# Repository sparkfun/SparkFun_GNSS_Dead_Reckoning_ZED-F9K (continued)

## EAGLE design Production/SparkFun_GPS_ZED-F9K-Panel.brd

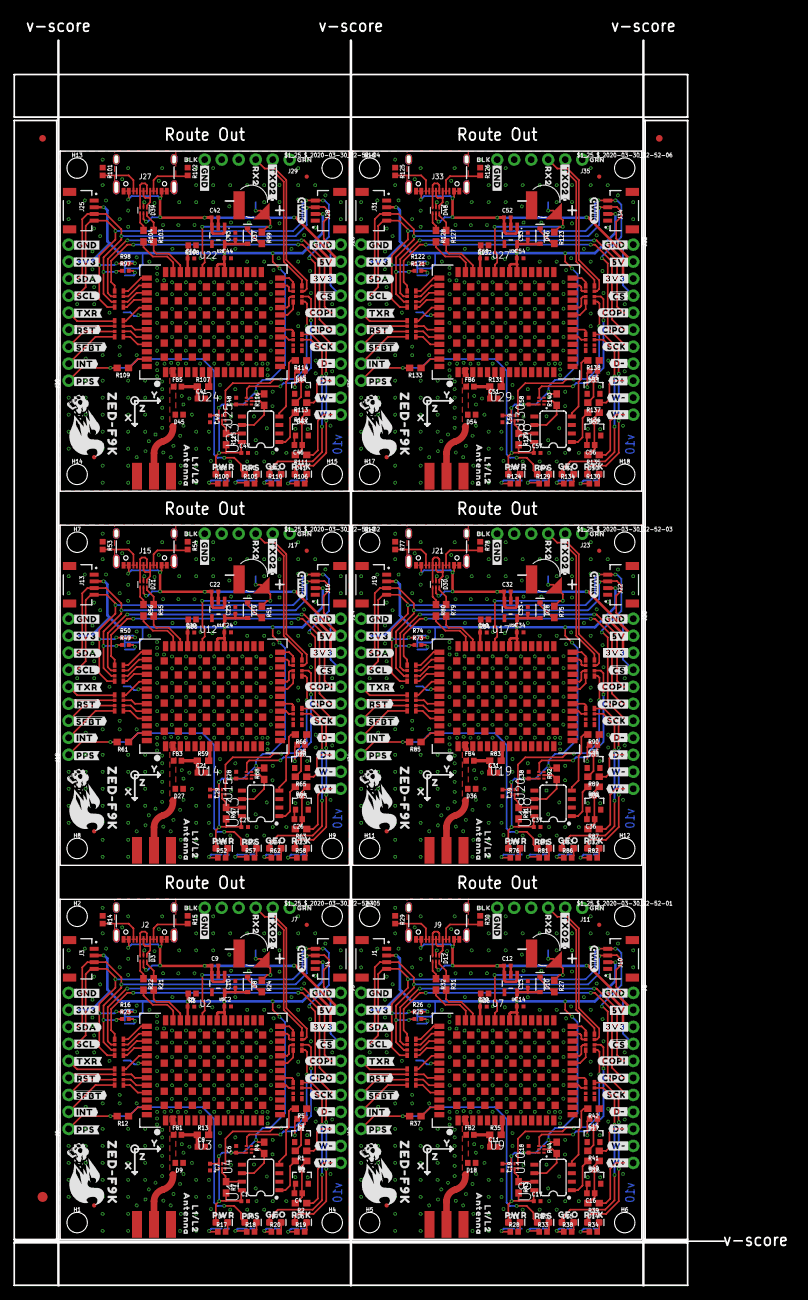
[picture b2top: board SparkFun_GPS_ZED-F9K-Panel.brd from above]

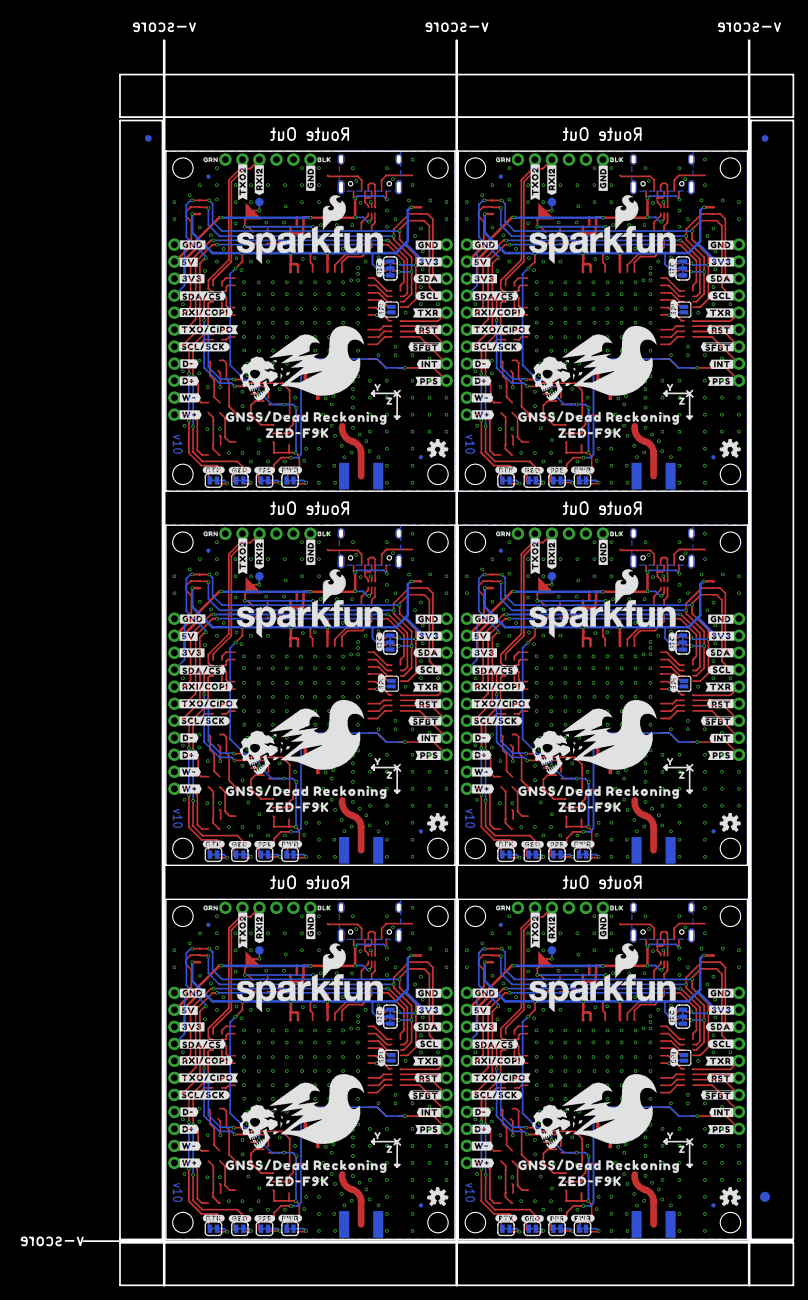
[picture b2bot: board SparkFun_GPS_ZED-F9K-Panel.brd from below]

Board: 2 copper layers, 106.0 x 185.9 mm, 894 parts (285 on the bottom side), 396 nets.

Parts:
$1_25_$_2020-03-30_22-52-01, $1_25_$_2020-03-30_22-52-02, $1_25_$_2020-03-30_22-52-03, $1_25_$_2020-03-30_22-52-04, $1_25_$_2020-03-30_22-52-05, $1_25_$_2020-03-30_22-52-06: STAND-OFFTIGHT; STAND-OFF-TIGHT
BT1, BT2, BT3, BT4, BT5, BT6: ML414H_IV01E_BATTERY; ML414H_IV01E
C1, C5, C6, C7, C17, C18, C19, C20, C27, C28, C29, C30, C37, C38, C39, C40, C47, C48, C49, C50, C57, C58, C59, C60: 0.1uF; 0402-TIGHT
C2, C9, C10, C12, C13, C14, C22, C23, C24, C32, C33, C34, C42, C43, C44, C52, C53, C54: 1.0uF; 0402-TIGHT
C3, C4, C15, C16, C25, C26, C35, C36, C45, C46, C55, C56: 1nF; 0402
C8, C11, C21, C31, C41, C51: 47pF; 0402
D1, D2, D16, D17, D25, D26, D34, D35, D43, D44, D52, D53: 15V; SOT23-3
D3, D12, D21, D30, D39, D48: PRTR5V0U2F; SOT886
D4, D11, D20, D29, D38, D47: RED; LED-0603
D5, D6, D7, D13, D14, D15, D22, D23, D24, D31, D32, D33, D40, D41, D42, D49, D50, D51: BLUE; LED-0603
D8, D10, D19, D28, D37, D46: 0.5A/40V/420mV; SOD-323
D9, D18, D27, D36, D45, D54: PESD0402; 0402
E1, E2, E3, E4, E5, E6: ANTENNA-SMA-GROUNDEDEDGE_SMA; SMA-EDGE
E$1, E$2, E$3, E$4: FIDUCIAL-1X2
E$5, E$6: FIDUCIAL-1.5X3
FB1, FB2, FB3, FB4, FB5, FB6: 120Ω; 0402
FD1, FD2, FD3, FD4, FD5, FD6, FD7, FD8, FD9, FD10, FD11, FD12, FD13, FD14, FD15, FD16, FD17, FD18, FD19, FD20, FD21, FD22, FD23, FD24: FIDUCIALUFIDUCIAL; FIDUCIAL-MICRO
GEO, GEO1, GEO2, GEO3, GEO4, GEO5: JUMPER-SMT_2_NC_TRACE_SILK; SMT-JUMPER_2_NC_TRACE_SILK
H1, H2, H3, H4, H5, H6, H7, H8, H9, H10, H11, H12, H13, H14, H15, H16, H17, H18: STAND-OFFTIGHT; STAND-OFF-TIGHT
I2C, I2C1, I2C2, I2C3, I2C4, I2C5: JUMPER-SMT_3_2-NC_TRACE_SILK; SMT-JUMPER_3_2-NC_TRACE_SILK
J1, J3, J4, J10, J13, J16, J19, J22, J25, J28, J31, J34: QWIIC_RIGHT_ANGLE; JST04_1MM_RA
J2, J9, J15, J21, J27, J33: USB-C-16P-2LAYER-PADS
J5, J8, J14, J20, J26, J32: 1X11_NO_SILK
J6, J12, J18, J24, J30, J36: 1X09_NO_SILK
J7, J11, J17, J23, J29, J35: 1X06_NO_SILK
LOGO1, LOGO6, LOGO9, LOGO12, LOGO15, LOGO18: OSHW-LOGOS; OSHW-LOGO-S
LOGO2, LOGO5, LOGO8, LOGO11, LOGO14, LOGO17: QWIIC_LOGO_4MM; QWIIC_4MM
LOGO3, LOGO4, LOGO7, LOGO10, LOGO13, LOGO16: SFE_LOGO_NAME_FLAME.2_INCH; SFE_LOGO_NAME_FLAME_.2
PPS, PPS1, PPS2, PPS3, PPS4, PPS5: JUMPER-SMT_2_NC_TRACE_SILK; SMT-JUMPER_2_NC_TRACE_SILK
PWR, PWR1, PWR2, PWR3, PWR4, PWR5: JUMPER-SMT_2_NC_TRACE_SILK; SMT-JUMPER_2_NC_TRACE_SILK
R1, R2, R24, R27, R39, R41, R51, R63, R65, R75, R87, R89, R99, R111, R113, R123, R135, R137: 3.3k; 0603
R3, R36, R60, R84, R108, R132: 100K; 0402
R4, R7, R43, R44, R67, R68, R91, R92, R115, R116, R139, R140: 910; 0603
R5, R6, R40, R42, R64, R66, R88, R90, R112, R114, R136, R138: 470; 0603
R8, R9, R10, R11, R45, R46, R47, R48, R69, R70, R71, R72, R93, R94, R95, R96, R117, R118, R119, R120, R141, R142, R143, R144: 33; 1206_RA
R12, R13, R35, R37, R59, R61, R83, R85, R107, R109, R131, R133: 33; 0603
R14, R15, R29, R30, R53, R54, R77, R78, R101, R102, R125, R126: 5.1k; 0402
R16, R23, R25, R26, R49, R50, R73, R74, R97, R98, R121, R122: 4.7k; 0402-TIGHT
R17, R18, R19, R20, R28, R33, R34, R38, R52, R57, R58, R62, R76, R81, R82, R86, R100, R105, R106, R110, R124, R129, R130, R134: 1KOHM-0402-1/16W-1%; 0402
R21, R22, R31, R32, R55, R56, R79, R80, R103, R104, R127, R128: 27; 0603
RTK, RTK1, RTK2, RTK3, RTK4, RTK5: JUMPER-SMT_2_NC_TRACE_SILK; SMT-JUMPER_2_NC_TRACE_SILK
SPI, SPI1, SPI2, SPI3, SPI4, SPI5: JUMPER-SMT_2_NO_SILK; SMT-JUMPER_2_NO_SILK
TP1, TP2, TP3, TP4, TP5, TP6: TEST-POINT3X5; PAD.03X.05
U1, U8, U13, U18, U23, U28: DUAL-OPTO_HCPL-073LSOIC-8; SO08
U2, U7, U12, U17, U22, U27: U-BLOX_ZED_F9K; UBLOX_ZED_F9K
U3, U4, U9, U10, U14, U15, U19, U20, U24, U25, U29, U30: UHS_INVERTER_SCHMITT_TRIGGERSIP6; SIP6
U5, U6, U11, U16, U21, U26: 3.3V; SOT23-5
U$1, U$81, U$154, U$227, U$300, U$373: PWR22
U$2, U$82, U$155, U$228, U$301, U$374: PPS21
U$3, U$83, U$156, U$229, U$302, U$375: GEO23
U$4, U$84, U$157, U$230, U$303, U$376: RTK24
U$5, U$85, U$158, U$231, U$304, U$377: #W##16
U$6, U$86, U$159, U$232, U$305, U$378: #W##15
U$7, U$14, U$22, U$37, U$55, U$92, U$101, U$109, U$110, U$121, U$165, U$174, U$182, U$183, U$194, U$238, U$247, U$255, U$256, U$267, U$311, U$320, U$328, U$329, U$340, U$384, U$393, U$401, U$402, U$413: #3V3#6
U$8, U$87, U$160, U$233, U$306, U$379: #D##13
U$9, U$88, U$161, U$234, U$307, U$380: #D##14
U$10, U$89, U$162, U$235, U$308, U$381: #SCK#12
U$11, U$90, U$163, U$236, U$309, U$382: #CIPO#10
U$12, U$91, U$164, U$237, U$310, U$383: #COPI#9
U$13, U$108, U$181, U$254, U$327, U$400: ##CS##11
U$15, U$24, U$93, U$111, U$166, U$184, U$239, U$257, U$312, U$330, U$385, U$403: #5V#1
U$16, U$17, U$25, U$36, U$44, U$58, U$94, U$95, U$100, U$112, U$120, U$137, U$167, U$168, U$173, U$185, U$193, U$210, U$240, U$241, U$246, U$258, U$266, U$283, U$313, U$314, U$319, U$331, U$339, U$356, U$386, U$387, U$392, U$404, U$412, U$429: #GND#0
U$18, U$96, U$169, U$242, U$315, U$388: #TXO2#20
U$19, U$20, U$29, U$75, U$147, U$148, U$220, U$221, U$293, U$294, U$366, U$367: DEAD#RECKONING#GPS#BOARD#SILK#FINAL#JPG
U$21, U$97, U$170, U$243, U$316, U$389: RX224
U$23, U$98, U$171, U$244, U$317, U$390: BLK225
U$26, U$99, U$172, U$245, U$318, U$391: GRN226
U$27, U$113, U$186, U$259, U$332, U$405: #SDA##CS##10
U$28, U$114, U$187, U$260, U$333, U$406: #RXI#COPI#8
U$30, U$115, U$188, U$261, U$334, U$407: #SCL#SCK#12
U$31, U$116, U$189, U$262, U$335, U$408: #D##6
U$32, U$76, U$149, U$222, U$295, U$368: X1
U$33, U$117, U$190, U$263, U$336, U$409: #D##7
U$34, U$118, U$191, U$264, U$337, U$410: #W##4
U$35, U$119, U$192, U$265, U$338, U$411: #W##5
U$38, U$122, U$195, U$268, U$341, U$414: #SDA#6
U$39, U$123, U$196, U$269, U$342, U$415: #SCL#7
U$40, U$124, U$197, U$270, U$343, U$416: #TXR#3
U$41, U$125, U$198, U$271, U$344, U$417: ##RST##16
U$42, U$126, U$199, U$272, U$345, U$418: ##SFBT##17
U$43, U$127, U$200, U$273, U$346, U$419: #INT#8
U$45, U$128, U$201, U$274, U$347, U$420: #PPS#0
U$46, U$129, U$202, U$275, U$348, U$421: #RTK#25
U$47, U$130, U$203, U$276, U$349, U$422: #GEO#24
U$48, U$131, U$204, U$277, U$350, U$423: #PPS#21
U$49, U$142, U$215, U$288, U$361, U$434: L1#L2229
U$50, U$52, U$77, U$78, U$150, U$151, U$223, U$224, U$296, U$297, U$369, U$370: Y2
U$51, U$132, U$205, U$278, U$351, U$424: #PWR#23
U$53, U$133, U$206, U$279, U$352, U$425: #SPI#22
U$54, U$134, U$207, U$280, U$353, U$426: #I2C#23
U$56, U$102, U$175, U$248, U$321, U$394: #SDA#12
U$57, U$63, U$79, U$80, U$152, U$153, U$225, U$226, U$298, U$299, U$371, U$372: Z0
U$59, U$135, U$208, U$281, U$354, U$427: #RXI2#227
U$60, U$136, U$209, U$282, U$355, U$428: #TXO2#1
U$61, U$138, U$211, U$284, U$357, U$430: BLK227
U$62, U$143, U$216, U$289, U$362, U$435: ANTENNA229
U$64, U$139, U$212, U$285, U$358, U$431: GRN228
U$65, U$140, U$213, U$286, U$359, U$432: GNSS#DEAD_RECKONING230
U$66, U$103, U$176, U$249, U$322, U$395: #SCL#13
U$67, U$104, U$177, U$250, U$323, U$396: #TXR#19
U$68, U$105, U$178, U$251, U$324, U$397: ##RST##17
U$69, U$106, U$179, U$252, U$325, U$398: ##SFBT##18
U$70, U$107, U$180, U$253, U$326, U$399: #INT#14
U$71, U$145, U$218, U$291, U$364, U$437: #PPS#20
U$72, U$73, U$141, U$144, U$214, U$217, U$287, U$290, U$360, U$363, U$433, U$436: ZED#F9K230
U$74, U$146, U$219, U$292, U$365, U$438: #TXO#CIPO#9

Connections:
3.3V: C1.1, C2.1, C5.1, C6.1, C7.1, C10.1, D4.A, D8.A, I2C.2, J3.2, J4.2, J5.3, J6.8, R3.2, R4.2, R7.2, U1.8, U2.P33, U2.P34, U2.P38, U3.P6, U4.P6, U5.5
3.3V1: C13.1, C14.1, C17.1, C18.1, C19.1, C20.1, D10.A, D11.A, I2C1.2, J1.2, J8.3, J10.2, J12.8, R36.2, R43.2, R44.2, U6.5, U7.P33, U7.P34, U7.P38, U8.8, U9.P6, U10.P6
3.3V2: C23.1, C24.1, C27.1, C28.1, C29.1, C30.1, D19.A, D20.A, I2C2.2, J13.2, J14.3, J16.2, J18.8, R60.2, R67.2, R68.2, U11.5, U12.P33, U12.P34, U12.P38, U13.8, U14.P6, U15.P6
3.3V3: C33.1, C34.1, C37.1, C38.1, C39.1, C40.1, D28.A, D29.A, I2C3.2, J19.2, J20.3, J22.2, J24.8, R84.2, R91.2, R92.2, U16.5, U17.P33, U17.P34, U17.P38, U18.8, U19.P6, U20.P6
3.3V4: C43.1, C44.1, C47.1, C48.1, C49.1, C50.1, D37.A, D38.A, I2C4.2, J25.2, J26.3, J28.2, J30.8, R108.2, R115.2, R116.2, U21.5, U22.P33, U22.P34, U22.P38, U23.8, U24.P6, U25.P6
3.3V5: C53.1, C54.1, C57.1, C58.1, C59.1, C60.1, D46.A, D47.A, I2C5.2, J31.2, J32.3, J34.2, J36.8, R132.2, R139.2, R140.2, U26.5, U27.P33, U27.P34, U27.P38, U28.8, U29.P6, U30.P6
!RESET: J6.4, R8.P2
!RESET1: J12.4, R46.P2
!RESET2: J18.4, R70.P2
!RESET3: J24.4, R94.P2
!RESET4: J30.4, R118.P2
!RESET5: J36.4, R142.P2
!SAFEBOOT: J6.3, R8.P3
!SAFEBOOT1: J12.3, R46.P3
!SAFEBOOT2: J18.3, R70.P3
!SAFEBOOT3: J24.3, R94.P3
!SAFEBOOT4: J30.3, R118.P3
!SAFEBOOT5: J36.3, R142.P3
DIR+: J5.9, R1.1
DIR+1: J8.9, R41.1
DIR+2: J14.9, R65.1
DIR+3: J20.9, R89.1
DIR+4: J26.9, R113.1
DIR+5: J32.9, R137.1
DIR_IN: R5.2, U1.4
DIR_IN1: R42.2, U8.4
DIR_IN2: R66.2, U13.4
DIR_IN3: R90.2, U18.4
DIR_IN4: R114.2, U23.4
DIR_IN5: R138.2, U28.4
DIR_INV: R4.1, U1.6, U4.P2
DIR_INV1: R44.1, U8.6, U10.P2
DIR_INV2: R68.1, U13.6, U15.P2
DIR_INV3: R92.1, U18.6, U20.P2
DIR_INV4: R116.1, U23.6, U25.P2
DIR_INV5: R140.1, U28.6, U30.P2
DIR_OUT: R10.P6, U4.P4
DIR_OUT1: R47.P6, U10.P4
DIR_OUT2: R71.P6, U15.P4
DIR_OUT3: R95.P6, U20.P4
DIR_OUT4: R119.P6, U25.P4
DIR_OUT5: R143.P6, U30.P4
DMINUS: R21.2, U2.P39
DMINUS1: R31.2, U7.P39
DMINUS2: R55.2, U12.P39
DMINUS3: R79.2, U17.P39
DMINUS4: R103.2, U22.P39
DMINUS5: R127.2, U27.P39
DPLUS: R22.2, U2.P40
DPLUS1: R32.2, U7.P40
DPLUS2: R56.2, U12.P40
DPLUS3: R80.2, U17.P40
DPLUS4: R104.2, U22.P40
DPLUS5: R128.2, U27.P40
D_SEL: SPI.1, U2.P47
D_SEL1: SPI1.1, U7.P47
D_SEL2: SPI2.1, U12.P47
D_SEL3: SPI3.1, U17.P47
D_SEL4: SPI4.1, U22.P47
D_SEL5: SPI5.1, U27.P47
GEOF_STAT: D7.A, R11.P7
GEOF_STAT1: D15.A, R48.P7
GEOF_STAT2: D24.A, R72.P7
GEOF_STAT3: D33.A, R96.P7
GEOF_STAT4: D42.A, R120.P7
GEOF_STAT5: D51.A, R144.P7
GND: BT1.-, C1.2, C2.2, C3.2, C4.2, C5.2, C6.2, C7.2, C8.2, C9.2, C10.2, D1.1, D2.1, D3.2, D9.1, E1.GND@0, E1.GND@1, E1.GND@2, E1.GND@3, GEO.1, J2.GND, J2.GND2, J3.1, J4.1, J5.1, J5.8, J5.10, J6.9, J7.6, PPS.1, PWR.1, R3.1, R14.1, R15.1, RTK.1, SPI.2, U1.2, U1.3, U1.5, U2.G1, U2.G2, U2.G3, U2.G4, U2.G5, U2.G6, U2.G7, U2.G8, U2.G9, U2.G10, U2.G11, U2.G12, U2.G13, U2.G14, U2.G15, U2.G16, U2.G17, U2.G18, U2.G19, U2.G20, U2.G21, U2.G22, U2.G23, U2.G24, U2.G25, U2.G26, U2.G27, U2.G28, U2.G29, U2.G30, U2.G31, U2.G32, U2.G33, U2.G34, U2.G35, U2.G36, U2.G37, U2.G38, U2.G39, U2.G40, U2.G41, U2.G42, U2.G43, U2.G44, U2.G45, U2.G46, U2.G47, U2.G48, U2.P1, U2.P3, U2.P12, U2.P14, U2.P32, U2.P37, U2.P41, U2.P48, U3.P3, U4.P3, U5.2
GND1: BT2.-, C11.2, C12.2, C13.2, C14.2, C15.2, C16.2, C17.2, C18.2, C19.2, C20.2, D12.2, D16.1, D17.1, D18.1, E2.GND@0, E2.GND@1, E2.GND@2, E2.GND@3, GEO1.1, J1.1, J8.1, J8.8, J8.10, J9.GND, J9.GND2, J10.1, J11.6, J12.9, PPS1.1, PWR1.1, R29.1, R30.1, R36.1, RTK1.1, SPI1.2, U6.2, U7.G1, U7.G2, U7.G3, U7.G4, U7.G5, U7.G6, U7.G7, U7.G8, U7.G9, U7.G10, U7.G11, U7.G12, U7.G13, U7.G14, U7.G15, U7.G16, U7.G17, U7.G18, U7.G19, U7.G20, U7.G21, U7.G22, U7.G23, U7.G24, U7.G25, U7.G26, U7.G27, U7.G28, U7.G29, U7.G30, U7.G31, U7.G32, U7.G33, U7.G34, U7.G35, U7.G36, U7.G37, U7.G38, U7.G39, U7.G40, U7.G41, U7.G42, U7.G43, U7.G44, U7.G45, U7.G46, U7.G47, U7.G48, U7.P1, U7.P3, U7.P12, U7.P14, U7.P32, U7.P37, U7.P41, U7.P48, U8.2, U8.3, U8.5, U9.P3, U10.P3
GND2: BT3.-, C21.2, C22.2, C23.2, C24.2, C25.2, C26.2, C27.2, C28.2, C29.2, C30.2, D21.2, D25.1, D26.1, D27.1, E3.GND@0, E3.GND@1, E3.GND@2, E3.GND@3, GEO2.1, J13.1, J14.1, J14.8, J14.10, J15.GND, J15.GND2, J16.1, J17.6, J18.9, PPS2.1, PWR2.1, R53.1, R54.1, R60.1, RTK2.1, SPI2.2, U11.2, U12.G1, U12.G2, U12.G3, U12.G4, U12.G5, U12.G6, U12.G7, U12.G8, U12.G9, U12.G10, U12.G11, U12.G12, U12.G13, U12.G14, U12.G15, U12.G16, U12.G17, U12.G18, U12.G19, U12.G20, U12.G21, U12.G22, U12.G23, U12.G24, U12.G25, U12.G26, U12.G27, U12.G28, U12.G29, U12.G30, U12.G31, U12.G32, U12.G33, U12.G34, U12.G35, U12.G36, U12.G37, U12.G38, U12.G39, U12.G40, U12.G41, U12.G42, U12.G43, U12.G44, U12.G45, U12.G46, U12.G47, U12.G48, U12.P1, U12.P3, U12.P12, U12.P14, U12.P32, U12.P37, U12.P41, U12.P48, U13.2, U13.3, U13.5, U14.P3, U15.P3
GND3: BT4.-, C31.2, C32.2, C33.2, C34.2, C35.2, C36.2, C37.2, C38.2, C39.2, C40.2, D30.2, D34.1, D35.1, D36.1, E4.GND@0, E4.GND@1, E4.GND@2, E4.GND@3, GEO3.1, J19.1, J20.1, J20.8, J20.10, J21.GND, J21.GND2, J22.1, J23.6, J24.9, PPS3.1, PWR3.1, R77.1, R78.1, R84.1, RTK3.1, SPI3.2, U16.2, U17.G1, U17.G2, U17.G3, U17.G4, U17.G5, U17.G6, U17.G7, U17.G8, U17.G9, U17.G10, U17.G11, U17.G12, U17.G13, U17.G14, U17.G15, U17.G16, U17.G17, U17.G18, U17.G19, U17.G20, U17.G21, U17.G22, U17.G23, U17.G24, U17.G25, U17.G26, U17.G27, U17.G28, U17.G29, U17.G30, U17.G31, U17.G32, U17.G33, U17.G34, U17.G35, U17.G36, U17.G37, U17.G38, U17.G39, U17.G40, U17.G41, U17.G42, U17.G43, U17.G44, U17.G45, U17.G46, U17.G47, U17.G48, U17.P1, U17.P3, U17.P12, U17.P14, U17.P32, U17.P37, U17.P41, U17.P48, U18.2, U18.3, U18.5, U19.P3, U20.P3
GND4: BT5.-, C41.2, C42.2, C43.2, C44.2, C45.2, C46.2, C47.2, C48.2, C49.2, C50.2, D39.2, D43.1, D44.1, D45.1, E5.GND@0, E5.GND@1, E5.GND@2, E5.GND@3, GEO4.1, J25.1, J26.1, J26.8, J26.10, J27.GND, J27.GND2, J28.1, J29.6, J30.9, PPS4.1, PWR4.1, R101.1, R102.1, R108.1, RTK4.1, SPI4.2, U21.2, U22.G1, U22.G2, U22.G3, U22.G4, U22.G5, U22.G6, U22.G7, U22.G8, U22.G9, U22.G10, U22.G11, U22.G12, U22.G13, U22.G14, U22.G15, U22.G16, U22.G17, U22.G18, U22.G19, U22.G20, U22.G21, U22.G22, U22.G23, U22.G24, U22.G25, U22.G26, U22.G27, U22.G28, U22.G29, U22.G30, U22.G31, U22.G32, U22.G33, U22.G34, U22.G35, U22.G36, U22.G37, U22.G38, U22.G39, U22.G40, U22.G41, U22.G42, U22.G43, U22.G44, U22.G45, U22.G46, U22.G47, U22.G48, U22.P1, U22.P3, U22.P12, U22.P14, U22.P32, U22.P37, U22.P41, U22.P48, U23.2, U23.3, U23.5, U24.P3, U25.P3
GND5: BT6.-, C51.2, C52.2, C53.2, C54.2, C55.2, C56.2, C57.2, C58.2, C59.2, C60.2, D48.2, D52.1, D53.1, D54.1, E6.GND@0, E6.GND@1, E6.GND@2, E6.GND@3, GEO5.1, J31.1, J32.1, J32.8, J32.10, J33.GND, J33.GND2, J34.1, J35.6, J36.9, PPS5.1, PWR5.1, R125.1, R126.1, R132.1, RTK5.1, SPI5.2, U26.2, U27.G1, U27.G2, U27.G3, U27.G4, U27.G5, U27.G6, U27.G7, U27.G8, U27.G9, U27.G10, U27.G11, U27.G12, U27.G13, U27.G14, U27.G15, U27.G16, U27.G17, U27.G18, U27.G19, U27.G20, U27.G21, U27.G22, U27.G23, U27.G24, U27.G25, U27.G26, U27.G27, U27.G28, U27.G29, U27.G30, U27.G31, U27.G32, U27.G33, U27.G34, U27.G35, U27.G36, U27.G37, U27.G38, U27.G39, U27.G40, U27.G41, U27.G42, U27.G43, U27.G44, U27.G45, U27.G46, U27.G47, U27.G48, U27.P1, U27.P3, U27.P12, U27.P14, U27.P32, U27.P37, U27.P41, U27.P48, U28.2, U28.3, U28.5, U29.P3, U30.P3
INT: J6.2, R8.P4
INT1: J12.2, R46.P4
INT2: J18.2, R70.P4
INT3: J24.2, R94.P4
INT4: J30.2, R118.P4
INT5: J36.2, R142.P4
unnamed: I2C.1, R23.2
unnamed: D8.C, R24.2
unnamed: I2C.3, R16.2
unnamed: D4.C, R17.2
unnamed: C8.1, FB1.2, R13.1
unnamed: D3.3, J2.A6, J2.B6
unnamed: D3.1, J2.A7, J2.B7
unnamed: PWR.2, R17.1
unnamed: D3.6, R21.1
unnamed: D3.4, R22.1
unnamed: R8.P7, U2.P49
unnamed: R8.P5, U2.P51
unnamed: D10.C, R27.2
unnamed: J2.B5, R14.2
unnamed: J2.A5, R15.2
unnamed: R9.P6, U2.P44
unnamed: R9.P5, U2.P45
unnamed: R8.P8, U2.P46
unnamed: R9.P8, U2.P42
unnamed: R9.P7, U2.P43
unnamed: R10.P1, U2.P27
unnamed: R19.1, RTK.2
unnamed: PPS.2, R18.1
unnamed: D5.C, R18.2
unnamed: D6.C, R19.2
unnamed: R10.P2, U2.P26
unnamed: R11.P2, U2.P19
unnamed: R11.P1, U2.P20
unnamed: R12.1, U2.P53
unnamed: R8.P6, U2.P50
unnamed: R10.P4, U2.P22
unnamed: R10.P3, U2.P23
unnamed: GEO.2, R20.1
unnamed: D7.C, R20.2
unnamed: C4.1, D2.3, R2.2, R6.1
unnamed: I2C1.1, R25.2
unnamed: C3.1, D1.3, R1.2, R5.1
unnamed: I2C1.3, R26.2
unnamed: J9.B5, R29.2
unnamed: J9.A5, R30.2
unnamed: R34.1, RTK1.2
unnamed: PPS1.2, R33.1
unnamed: D13.C, R33.2
unnamed: D14.C, R34.2
unnamed: D11.C, R28.2
unnamed: PWR1.2, R28.1
unnamed: C11.1, FB2.2, R35.1
unnamed: D12.3, J9.A6, J9.B6
unnamed: D12.1, J9.A7, J9.B7
unnamed: D12.6, R31.1
unnamed: D12.4, R32.1
unnamed: R46.P7, U7.P49
unnamed: R46.P5, U7.P51
unnamed: R45.P6, U7.P44
unnamed: R45.P5, U7.P45
unnamed: R46.P8, U7.P46
unnamed: R45.P8, U7.P42
unnamed: R45.P7, U7.P43
unnamed: R47.P1, U7.P27
unnamed: R47.P2, U7.P26
unnamed: R48.P2, U7.P19
unnamed: R48.P1, U7.P20
unnamed: R37.1, U7.P53
unnamed: R46.P6, U7.P50
unnamed: R47.P4, U7.P22
unnamed: R47.P3, U7.P23
unnamed: GEO1.2, R38.1
unnamed: D15.C, R38.2
unnamed: C16.1, D16.3, R39.2, R40.1
unnamed: C15.1, D17.3, R41.2, R42.1
unnamed: D19.C, R51.2
unnamed: I2C2.1, R49.2
unnamed: I2C2.3, R50.2
unnamed: J15.B5, R53.2
unnamed: J15.A5, R54.2
unnamed: R58.1, RTK2.2
unnamed: PPS2.2, R57.1
unnamed: D22.C, R57.2
unnamed: D23.C, R58.2
unnamed: D20.C, R52.2
unnamed: PWR2.2, R52.1
unnamed: C21.1, FB3.2, R59.1
unnamed: D21.3, J15.A6, J15.B6
unnamed: D21.1, J15.A7, J15.B7
unnamed: D21.6, R55.1
unnamed: D21.4, R56.1
unnamed: R70.P7, U12.P49
unnamed: R70.P5, U12.P51
unnamed: R69.P6, U12.P44
unnamed: R69.P5, U12.P45
unnamed: R70.P8, U12.P46
unnamed: R69.P8, U12.P42
unnamed: R69.P7, U12.P43
unnamed: R71.P1, U12.P27
unnamed: R71.P2, U12.P26
unnamed: R72.P2, U12.P19
unnamed: R72.P1, U12.P20
unnamed: R61.1, U12.P53
unnamed: R70.P6, U12.P50
unnamed: R71.P4, U12.P22
unnamed: R71.P3, U12.P23
unnamed: GEO2.2, R62.1
unnamed: D24.C, R62.2
unnamed: C26.1, D25.3, R63.2, R64.1
unnamed: C25.1, D26.3, R65.2, R66.1
unnamed: D28.C, R75.2
unnamed: I2C3.1, R73.2
unnamed: I2C3.3, R74.2
unnamed: J21.B5, R77.2
unnamed: J21.A5, R78.2
unnamed: R82.1, RTK3.2
unnamed: PPS3.2, R81.1
unnamed: D31.C, R81.2
unnamed: D32.C, R82.2
unnamed: D29.C, R76.2
unnamed: PWR3.2, R76.1
unnamed: C31.1, FB4.2, R83.1
unnamed: D30.3, J21.A6, J21.B6
unnamed: D30.1, J21.A7, J21.B7
unnamed: D30.6, R79.1
unnamed: D30.4, R80.1
unnamed: R94.P7, U17.P49
unnamed: R94.P5, U17.P51
unnamed: R93.P6, U17.P44
unnamed: R93.P5, U17.P45
unnamed: R94.P8, U17.P46
unnamed: R93.P8, U17.P42
unnamed: R93.P7, U17.P43
unnamed: R95.P1, U17.P27
unnamed: R95.P2, U17.P26
unnamed: R96.P2, U17.P19
unnamed: R96.P1, U17.P20
unnamed: R85.1, U17.P53
unnamed: R94.P6, U17.P50
unnamed: R95.P4, U17.P22
unnamed: R95.P3, U17.P23
unnamed: GEO3.2, R86.1
unnamed: D33.C, R86.2
unnamed: C36.1, D34.3, R87.2, R88.1
unnamed: C35.1, D35.3, R89.2, R90.1
unnamed: D37.C, R99.2
unnamed: I2C4.1, R97.2
unnamed: I2C4.3, R98.2
unnamed: J27.B5, R101.2
unnamed: J27.A5, R102.2
unnamed: R106.1, RTK4.2
unnamed: PPS4.2, R105.1
unnamed: D40.C, R105.2
unnamed: D41.C, R106.2
unnamed: D38.C, R100.2
unnamed: PWR4.2, R100.1
unnamed: C41.1, FB5.2, R107.1
unnamed: D39.3, J27.A6, J27.B6
unnamed: D39.1, J27.A7, J27.B7
unnamed: D39.6, R103.1
unnamed: D39.4, R104.1
unnamed: R118.P7, U22.P49
unnamed: R118.P5, U22.P51
unnamed: R117.P6, U22.P44
unnamed: R117.P5, U22.P45
unnamed: R118.P8, U22.P46
unnamed: R117.P8, U22.P42
unnamed: R117.P7, U22.P43
unnamed: R119.P1, U22.P27
unnamed: R119.P2, U22.P26
unnamed: R120.P2, U22.P19
unnamed: R120.P1, U22.P20
unnamed: R109.1, U22.P53
unnamed: R118.P6, U22.P50
unnamed: R119.P4, U22.P22
unnamed: R119.P3, U22.P23
unnamed: GEO4.2, R110.1
unnamed: D42.C, R110.2
unnamed: C46.1, D43.3, R111.2, R112.1
unnamed: C45.1, D44.3, R113.2, R114.1
unnamed: D46.C, R123.2
unnamed: I2C5.1, R121.2
unnamed: I2C5.3, R122.2
unnamed: J33.B5, R125.2
unnamed: J33.A5, R126.2
unnamed: R130.1, RTK5.2
unnamed: PPS5.2, R129.1
unnamed: D49.C, R129.2
unnamed: D50.C, R130.2
unnamed: D47.C, R124.2
unnamed: PWR5.2, R124.1
unnamed: C51.1, FB6.2, R131.1
unnamed: D48.3, J33.A6, J33.B6
unnamed: D48.1, J33.A7, J33.B7
unnamed: D48.6, R127.1
unnamed: D48.4, R128.1
unnamed: R142.P7, U27.P49
unnamed: R142.P5, U27.P51
unnamed: R141.P6, U27.P44
unnamed: R141.P5, U27.P45
unnamed: R142.P8, U27.P46
unnamed: R141.P8, U27.P42
unnamed: R141.P7, U27.P43
unnamed: R143.P1, U27.P27
unnamed: R143.P2, U27.P26
unnamed: R144.P2, U27.P19
unnamed: R144.P1, U27.P20
unnamed: R133.1, U27.P53
unnamed: R142.P6, U27.P50
unnamed: R143.P4, U27.P22
unnamed: R143.P3, U27.P23
unnamed: GEO5.2, R134.1
unnamed: D51.C, R134.2
unnamed: C56.1, D52.3, R135.2, R136.1
unnamed: C55.1, D53.3, R137.2, R138.1
PPS: D5.A, J6.1, R12.2
PPS1: D13.A, J12.1, R37.2
PPS2: D22.A, J18.1, R61.2
PPS3: D31.A, J24.1, R85.2
PPS4: D40.A, J30.1, R109.2
PPS5: D49.A, J36.1, R133.2
RF_IN: D9.2, E1.SIG, FB1.1, U2.P2
RF_IN1: D18.2, E2.SIG, FB2.1, U7.P2
RF_IN2: D27.2, E3.SIG, FB3.1, U12.P2
RF_IN3: D36.2, E4.SIG, FB4.1, U17.P2
RF_IN4: D45.2, E5.SIG, FB5.1, U22.P2
RF_IN5: D54.2, E6.SIG, FB6.1, U27.P2
RTK_STAT: D6.A, R11.P8
RTK_STAT1: D14.A, R48.P8
RTK_STAT2: D23.A, R72.P8
RTK_STAT3: D32.A, R96.P8
RTK_STAT4: D41.A, R120.P8
RTK_STAT5: D50.A, R144.P8
RXI1: J11.3, R47.P7
RXI2: J7.3, R10.P7
RXI3: J17.3, R71.P7
RXI4: J23.3, R95.P7
RXI5: J29.3, R119.P7
RXI6: J35.3, R143.P7
RXI/COPI: J5.5, R9.P2
RXI/COPI1: J8.5, R45.P2
RXI/COPI2: J14.5, R69.P2
RXI/COPI3: J20.5, R93.P2
RXI/COPI4: J26.5, R117.P2
RXI/COPI5: J32.5, R141.P2
SCL/CLK: J3.4, J4.4, J5.7, J6.6, R9.P4, R16.1
SCL/CLK1: J1.4, J8.7, J10.4, J12.6, R26.1, R45.P4
SCL/CLK2: J13.4, J14.7, J16.4, J18.6, R50.1, R69.P4
SCL/CLK3: J19.4, J20.7, J22.4, J24.6, R74.1, R93.P4
SCL/CLK4: J25.4, J26.7, J28.4, J30.6, R98.1, R117.P4
SCL/CLK5: J31.4, J32.7, J34.4, J36.6, R122.1, R141.P4
SDA/!CS: J3.3, J4.3, J5.4, J6.7, R9.P3, R23.1
SDA/!CS1: J1.3, J8.4, J10.3, J12.7, R25.1, R45.P3
SDA/!CS2: J13.3, J14.4, J16.3, J18.7, R49.1, R69.P3
SDA/!CS3: J19.3, J20.4, J22.3, J24.7, R73.1, R93.P3
SDA/!CS4: J25.3, J26.4, J28.3, J30.7, R97.1, R117.P3
SDA/!CS5: J31.3, J32.4, J34.3, J36.7, R121.1, R141.P3
SHIELD: J2.SHLD1, J2.SHLD2, J2.SHLD3, J2.SHLD4
SHIELD1: J9.SHLD1, J9.SHLD2, J9.SHLD3, J9.SHLD4
SHIELD2: J15.SHLD1, J15.SHLD2, J15.SHLD3, J15.SHLD4
SHIELD3: J21.SHLD1, J21.SHLD2, J21.SHLD3, J21.SHLD4
SHIELD4: J27.SHLD1, J27.SHLD2, J27.SHLD3, J27.SHLD4
SHIELD5: J33.SHLD1, J33.SHLD2, J33.SHLD3, J33.SHLD4
TXO1: J11.2, R47.P8
TXO2: J7.2, R10.P8
TXO3: J17.2, R71.P8
TXO4: J23.2, R95.P8
TXO5: J29.2, R119.P8
TXO6: J35.2, R143.P8
TXO/CIPO: J5.6, R9.P1
TXO/CIPO1: J8.6, R45.P1
TXO/CIPO2: J14.6, R69.P1
TXO/CIPO3: J20.6, R93.P1
TXO/CIPO4: J26.6, R117.P1
TXO/CIPO5: J32.6, R141.P1
TX_READY: J6.5, R8.P1
TX_READY1: J12.5, R46.P1
TX_READY2: J18.5, R70.P1
TX_READY3: J24.5, R94.P1
TX_READY4: J30.5, R118.P1
TX_READY5: J36.5, R142.P1
VIN: C9.1, D3.5, J2.VBUS1, J2.VBUS2, J5.2, U5.1, U5.3
VIN1: C12.1, D12.5, J8.2, J9.VBUS1, J9.VBUS2, U6.1, U6.3
VIN2: C22.1, D21.5, J14.2, J15.VBUS1, J15.VBUS2, U11.1, U11.3
VIN3: C32.1, D30.5, J20.2, J21.VBUS1, J21.VBUS2, U16.1, U16.3
VIN4: C42.1, D39.5, J26.2, J27.VBUS1, J27.VBUS2, U21.1, U21.3
VIN5: C52.1, D48.5, J32.2, J33.VBUS1, J33.VBUS2, U26.1, U26.3
V_BATT: BT1.+, R24.1, TP1.1, U2.P36
V_BATT1: BT2.+, R27.1, TP2.1, U7.P36
V_BATT2: BT3.+, R51.1, TP3.1, U12.P36
V_BATT3: BT4.+, R75.1, TP4.1, U17.P36
V_BATT4: BT5.+, R99.1, TP5.1, U22.P36
V_BATT5: BT6.+, R123.1, TP6.1, U27.P36
V_RF: R13.2, U2.P7
V_RF1: R35.2, U7.P7
V_RF2: R59.2, U12.P7
V_RF3: R83.2, U17.P7
V_RF4: R107.2, U22.P7
V_RF5: R131.2, U27.P7
WT+: J5.11, R2.1
WT+1: J8.11, R39.1
WT+2: J14.11, R63.1
WT+3: J20.11, R87.1
WT+4: J26.11, R111.1
WT+5: J32.11, R135.1
WT_IN: R6.2, U1.1
WT_IN1: R40.2, U8.1
WT_IN2: R64.2, U13.1
WT_IN3: R88.2, U18.1
WT_IN4: R112.2, U23.1
WT_IN5: R136.2, U28.1
WT_INV: R7.1, U1.7, U3.P2
WT_INV1: R43.1, U8.7, U9.P2
WT_INV2: R67.1, U13.7, U14.P2
WT_INV3: R91.1, U18.7, U19.P2
WT_INV4: R115.1, U23.7, U24.P2
WT_INV5: R139.1, U28.7, U29.P2
WT_OUT: R10.P5, U3.P4
WT_OUT1: R47.P5, U9.P4
WT_OUT2: R71.P5, U14.P4
WT_OUT3: R95.P5, U19.P4
WT_OUT4: R119.P5, U24.P4
WT_OUT5: R143.P5, U29.P4

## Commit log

2021-09-27 Initial Commit - fully routed and silked board
2021-09-27 Updates libraries, replaces F9R with F9K, fixes some text in schematic, deletes blank sheets in schematic
2021-09-27 Updates script being used
2021-09-28 Moves traces for better ground pour and to reduce cross talk
    * Replaces all capacitors with smaller footprint
    * Replaces 2.2K resistors with 4.7K resistors
2021-09-28 Adds some leftover adjustments from the last commit
2021-09-29 Flips FTDI header, adds testpoint for VBAT, fixes dimension line width
2021-09-29 Changes name of I2C jumper to I2C, it was previously JP6
2021-10-01 Small changes
2021-10-01 Panel
2021-10-01 Fixes TXO/COPI silk to read TXO/CIPO
2021-10-01 Re-panelizes after silk change
2021-10-01 Removes old zip file
2021-10-04 Adds new panel from branch
2021-11-16 Adds PROD-ID to optoisolator
